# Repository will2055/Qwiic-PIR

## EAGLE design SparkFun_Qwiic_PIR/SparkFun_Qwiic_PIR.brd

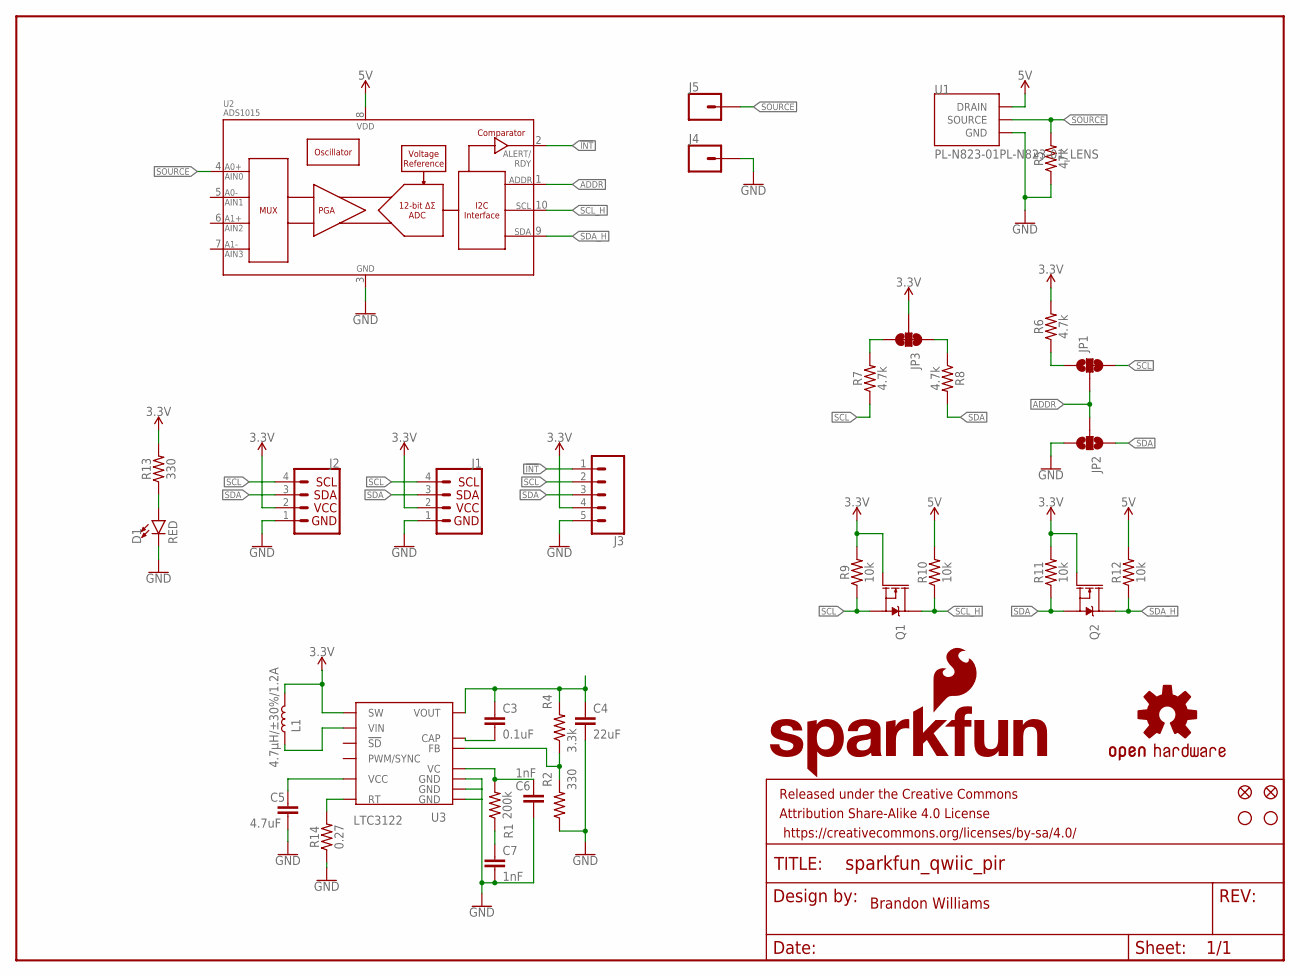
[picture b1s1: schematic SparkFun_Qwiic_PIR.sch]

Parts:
C3: 0.1uF; 0603
C4: 22uF; 0805
C5: 4.7uF; 1206
C6, C7: 1nF; 0603
D1: RED; LED-0603
FD1, FD2: FIDUCIAL0.2MM; FIDUCIAL-0.2MM
FRAME1: FRAME-LETTERNO_PACKAGE; DUMMY
H1, H2: STAND-OFFTIGHT; STAND-OFF-TIGHT
J1, J2: QWIIC_RIGHT_ANGLE; JST04_1MM_RA
J3: CONN_05NO_SILK; 1X05_NO_SILK
J4, J5: CONN_01PTH_NO_SILK_YES_STOP; 1X01_NO_SILK
JP1: JUMPER-SMT_3_1-NC_TRACE_SILK; SMT-JUMPER_3_1-NC_TRACE_SILK
JP2: JUMPER-SMT_3_NO_SILK; SMT-JUMPER_3_NO_SILK
JP3: JUMPER-SMT_3_2-NC_TRACE_SILK; SMT-JUMPER_3_2-NC_TRACE_SILK
L1: 4.7µH/±30%/1.2A; INDUCTOR_4.7UH
LOGO1: OSHW-LOGOMINI; OSHW-LOGO-MINI
LOGO3: SFE_LOGO_NAME_FLAME.2_INCH; SFE_LOGO_NAME_FLAME_.2
Q1, Q2: 220mA/50V/3.5Ω; SOT23-3
R1: 200k; 0603
R2, R13: 330; 0603
R4: 3.3k; 0603
R5: 47k; 0603
R6, R7, R8: 4.7k; 0603
R9, R10, R11, R12: 10k; 0402-TIGHT
R14: 0.27; 0603
U1: PL-N823-01PL-N823-01_LENS; PL-N823-01_LENS
U2: ADS1015; MSOP10
U3: LTC3122; LTC3122EDE#PBF

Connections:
3.3V: J1.2, J2.2, J3.4, JP3.2, L1.P$2 (2), Q1.1 (G), Q2.1 (G), R6.2, R9.2, R11.2, R13.2, U3.P$1 (SW)
5V: R10.2, R12.2, U1.DRAIN, U2.8 (VDD)
!INT: J3.1, U2.2 (ALERT/RDY)
ADDR: JP1.2, JP2.2, U2.1 (ADDR)
GND: C4.2, C5.2, C6.2, C7.2, D1.C, J1.1, J2.1, J3.5, J4.1, JP2.3, R2.1, R5.1, R14.1, U1.GND@1 (GND), U1.GND@2 (GND), U2.3 (VSS), U3.P$2 (GND), U3.P$10 (GND), U3.P$13 (GND)
unnamed: C5.1, U3.P$5 (VCC)
unnamed: JP1.1, R6.1
unnamed: L1.P$1 (1), U3.P$3 (VIN)
unnamed: D1.A, R13.1
unnamed: R14.2, U3.P$6 (RT)
unnamed: C3.1, C4.1, R4.2, U3.P$11 (VOUT)
unnamed: C3.2, U3.P$12 (CAP)
unnamed: JP3.1, R8.1
unnamed: JP3.3, R7.2
unnamed: R2.2, R4.1, U3.P$8 (FB)
unnamed: C6.1, R1.2, U3.P$7 (VC)
unnamed: C7.1, R1.1
SCL: J1.4, J2.4, J3.2, JP1.3, Q1.2 (S), R7.1, R9.1
SCL_H: Q1.3 (D), R10.1, U2.10 (SCL)
SDA: J1.3, J2.3, J3.3, JP2.1, Q2.2 (S), R8.2, R11.1
SDA_H: Q2.3 (D), R12.1, U2.9 (SDA)
SOURCE: J5.1, R5.2, U1.SOURCE, U2.4 (AIN0)

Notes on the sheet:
Brandon Williams

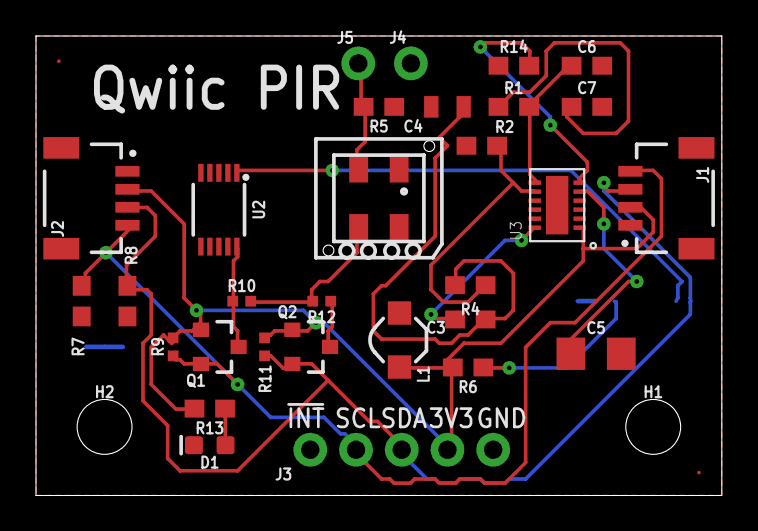
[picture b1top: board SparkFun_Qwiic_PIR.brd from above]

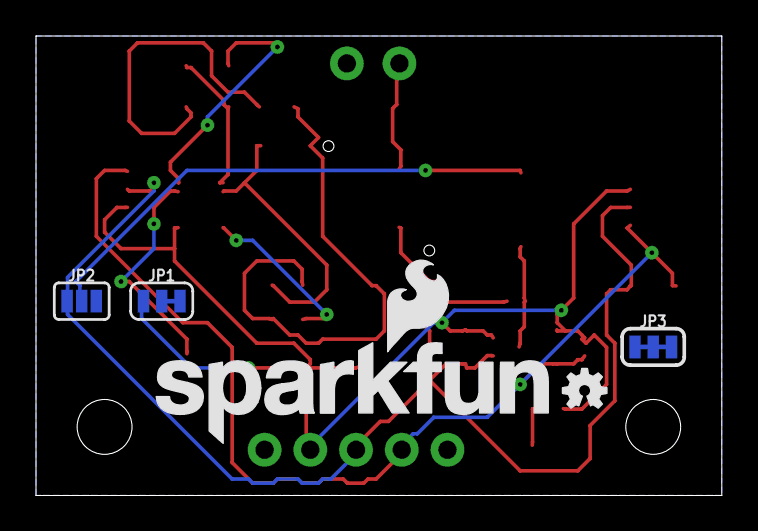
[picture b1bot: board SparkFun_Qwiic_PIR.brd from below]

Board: 2 copper layers, 38.1 x 25.5 mm, 40 parts (5 on the bottom side), 22 nets.

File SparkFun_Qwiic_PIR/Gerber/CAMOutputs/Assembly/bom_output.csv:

Qty, PROD_ID, Names, Value, Package,,,,Part Number,Added to Cart
1, CAP-11330, C1, 10uF,805,,,,1276-6456-2-ND,?
2, CAP-00868, C2, C3, 1.0uF,603,,,1276-1243-2-ND,?
1, CAP-14464, C4, 22uF,603,,,,490-7612-2-ND,?
1, DIO-00819, D1, RED, LED-0603,,,,?754-1122-1-ND? ,?
2, CONN-13694, J1, J2, QWIIC_RIGHT_ANGLE, JST04_1MM_RA,,,PRT-14417 ,SFE
1, NDUC-10146, L1, 4.7µH/±30%/1.2A, INDUCTOR_4.7UH,,,,308-2297-1-ND?,?
2, TRANS-00830, Q1, Q2, 220mA/50V/3.5Ω, SOT23-3,,,BSS138LT,?
2, RES-09385, R1, R2, 200k,603,,,311-200KHRTR-ND,?
2, RES-10054, R3, R4, 2.0M,603,,,311-2.0MGRCT-ND?,?
1, RES-07871, R5, 47k,603,,,,311-47KGRCT-ND ,?
3, RES-07857, R6, R7, R8, 4.7k,603,,311-4.7KGRCT-ND ,?
4, RES-14241, R9, R10, R11, R12, 10k, 0402-TIGHT,311-10.0KLRTR-ND,?
1, RES-00818, R13,330,603,,,,P330HCT-ND,?
1, , U1, PL-N823-01PL-N823-01_LENS, PL-N823-01_LENS,,,,,SFE
1, IC-12270, U2, ADS1015, MSOP10,,,,296-25227-2-ND,?
1, IC-10035, U3, TPS61200, QFN-10_PAD,,,,296-21663-2-ND,?

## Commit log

2020-03-12 Upload HW board files
2020-03-15 Uploaded LTC3122 Eagle Library
    LTC3122EDE#PBF
    15V - Boost IC
2020-03-16 Upload 15V revision with LTC3122 Boost IC

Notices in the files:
parts and their libraries:
SparkFun-Capacitors: Licensing: Creative Commons ShareAlike 4.0 International - https://creativecommons.org/licenses/by-sa/4.0
SparkFun-Aesthetics: Released under the Creative Commons Attribution Share-Alike 4.0 License
SparkFun-Aesthetics: https://creativecommons.org/licenses/by-sa/4.0
